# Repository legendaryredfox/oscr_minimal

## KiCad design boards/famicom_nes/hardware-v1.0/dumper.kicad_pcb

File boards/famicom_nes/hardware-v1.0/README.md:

# famicom_nes v1.0

Versão **v1.0** da placa [`famicom_nes`](../README.md): shield 100% THT para Arduino Mega 2560 R3, só USB. Versão anterior, mantida ao lado da mais nova.

| | |
|---|---|
| Slots | Famicom (60p) e NES (72p) em paralelo, 5 V; **um cartucho por vez, em um slot só** |
| Circuitos | Si5351, sem PIC. |
| Tamanho | 117,1 × 89,1 mm |
| Projeto KiCad | [`hardware-v1.0/`](.) (`dumper.kicad_pro`, `.kicad_sch`, `.kicad_pcb`) |
| Fábrica (JLCPCB) | `../fab/gerbers-v1.0/`, `../fab/dumper-v1.0-jlcpcb.zip` |
| Renders | `render-cima.png`, `render-baixo.png` |
| Estado | Nada montado nem testado com cartucho; revisar o layout no KiCad antes de encomendar |

## Troca de cartucho

O 5V dos slots vai direto do Mega e **não é cortado por software** (o desligamento por software foi retirado, D139). Para trocar o cartucho, **desligue a placa tirando o cabo USB** do Mega; nunca com a USB ligada.

## Proteção de corrente e tensão (D138)

**F1: fusível de vidro 5×20 mm de 500 mA (ação rápida) em suporte de clipes, opcional.** O suporte é de furo passante (Littelfuse série 100 ou equivalente) e o fusível queimado se troca **sem solda**; fica em série com o 5 V que a placa recebe do Mega Um curto no cartucho queima o fusível e protege a placa, o Mega e a porta USB. A queda é de 0,1 a 0,2 V a 200 mA (o SA-1 do SNES continua abaixo de ~5,2 V). **Sem o fusível no suporte a placa fica sem 5 V** (um fio no lugar dele também serve). Ele limita corrente e não protege contra tensão errada.

## Lista de peças

| Referências | Valor | Footprint | Qtd |
|---|---|---|---|
| A1 | Mega2560_R3_Shield | `dumper:Mega2560_R3_Shield` | 1 |
| C1 | 470u/16V | `Capacitor_THT:CP_Radial_D8.0mm_P3.50mm` | 1 |
| C2,C3 | 100n | `Capacitor_THT:C_Disc_D5.0mm_W2.5mm_P5.00mm` | 2 |
| D1 | LED 3mm | `LED_THT:LED_D3.0mm` | 1 |
| F1 | Fusivel 5x20 500mA | `Fuse:Fuseholder_Littelfuse_100_series_5x20mm` | 1 |
| FC1 | FC_Slot | `dumper:FC_Slot` | 1 |
| FLG1,FLG2 | PWR_FLAG | `` | 2 |
| NES1 | NES_Slot | `dumper:NES_Slot` | 1 |
| R1 | 220R | `Resistor_THT:R_Axial_DIN0207_L6.3mm_D2.5mm_P10.16mm_Horizontal` | 1 |
| U1 | Si5351_Module | `Connector_PinSocket_2.54mm:PinSocket_1x07_P2.54mm_Vertical` | 1 |

Gerada do esquemático desta versão (`kicad-cli sch export bom`). Peças marcadas DNP ou opcionais: `docs/bom.md` da placa.

## Verificação e fábrica (da raiz do repositório)

```
python3 tools/check_netlist.py --board famicom_nes boards/famicom_nes/hardware-v1.0/dumper.kicad_sch
kicad-cli sch erc boards/famicom_nes/hardware-v1.0/dumper.kicad_sch
kicad-cli pcb drc boards/famicom_nes/hardware-v1.0/dumper.kicad_pcb
tools/export_fab.sh famicom_nes v1.0
tools/render_board.sh famicom_nes v1.0 v1.1
```

Mais: [README da placa](../README.md), [`docs/`](../docs/).

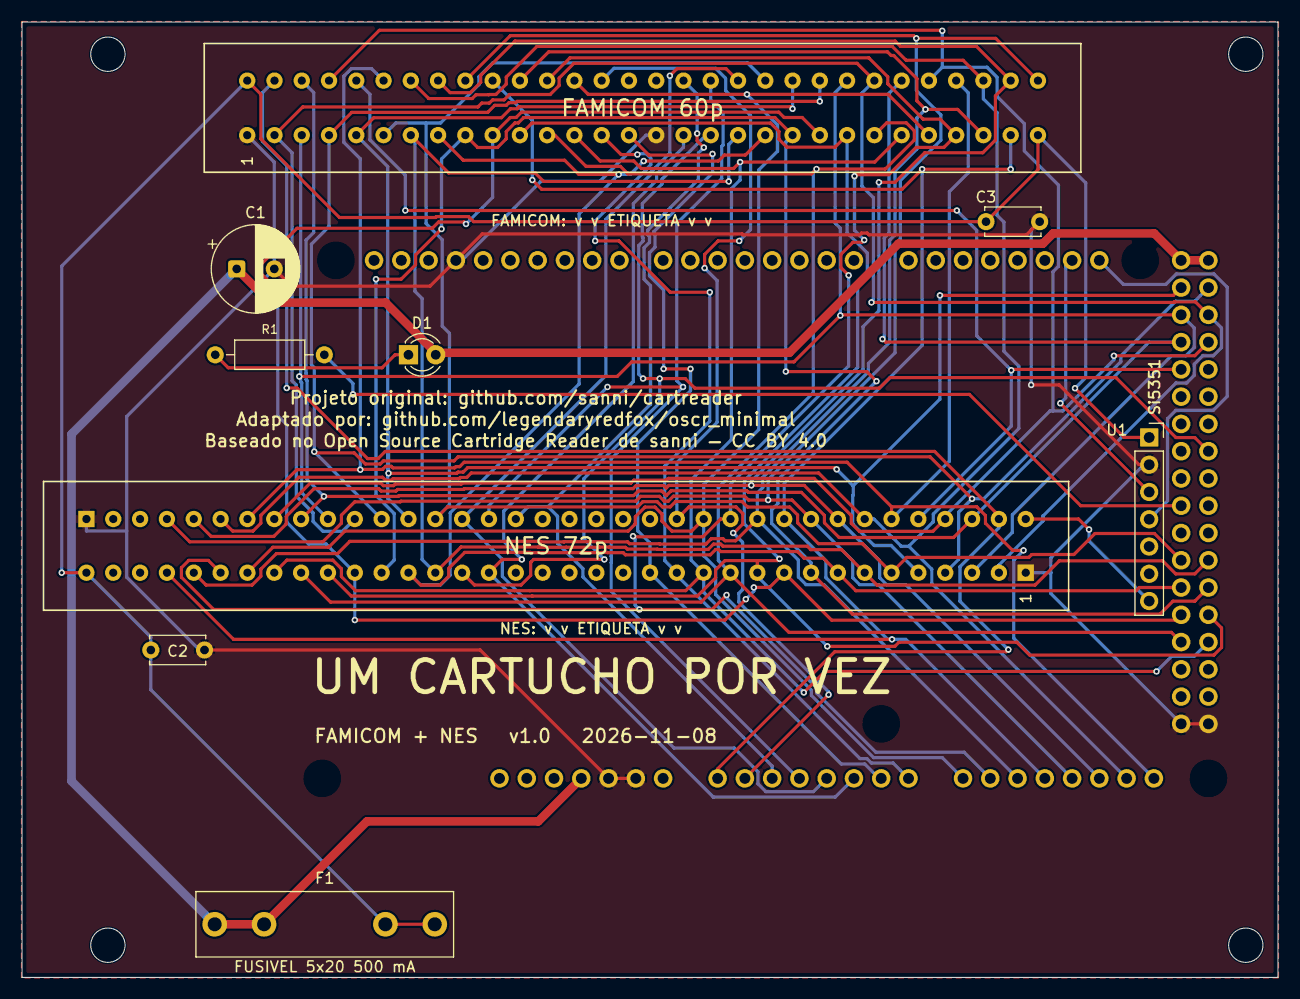
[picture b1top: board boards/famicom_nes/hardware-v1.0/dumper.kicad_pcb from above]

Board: 2 copper layers, 117.0 x 89.0 mm, 14 parts (0 on the bottom side), 40 nets.

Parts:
A1: Mega2560_R3_Shield
C1: 470u/16V; CP_Radial_D8.0mm_P3.50mm
C2, C3: 100n; C_Disc_D5.0mm_W2.5mm_P5.00mm
D1: LED 3mm; LED_D3.0mm
F1: Fusivel 5x20 500mA; Fuseholder_Littelfuse_100_series_5x20mm
FC1: FC_Slot
MH1, MH2, MH3, MH4: MountingHole_3.2mm; MountingHole_3.2mm_M3
NES1: NES_Slot
R1: 220R; R_Axial_DIN0207_L6.3mm_D2.5mm_P10.16mm_Horizontal
U1: Si5351_Module; PinSocket_1x07_P2.54mm_Vertical

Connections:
+5V: A1.5V1, A1.5V3, A1.5V4, C1.1, D1.2, F1.1
+5V_CART: C2.1, C3.1, F1.2, FC1.30, FC1.31, NES1.36, U1.1
/A0: A1.A0, FC1.32, NES1.38
/A1: A1.A1, FC1.44, NES1.50
/A2: A1.A2, FC1.47, NES1.56
/A3: A1.A3, FC1.48, NES1.57
/A4: A1.A4, FC1.49, NES1.58
/A5: A1.A5, FC1.17, NES1.21
/A6: A1.A6, FC1.15, NES1.15
/A7: A1.A7, FC1.14, NES1.14
/A8: A1.A8, FC1.26, FC1.43, NES1.30, NES1.49
/A9: A1.A9, FC1.27, FC1.42, NES1.31, NES1.48
/A10: A1.A10, FC1.28, FC1.41, NES1.32, NES1.47
/A11: A1.A11, FC1.29, FC1.40, NES1.33, NES1.46
/A12: A1.A12, FC1.39, FC1.60, NES1.45, NES1.69
/A13: A1.A13, FC1.38, FC1.59, NES1.44, NES1.68
/A14: A1.A14, FC1.37, FC1.58, NES1.43, NES1.67
/A15: A1.A15, FC1.36, FC1.57, NES1.42, NES1.66
/CLK0: NES1.37, U1.7
/D22: A1.D22, FC1.5, FC1.51, NES1.5, NES1.60
/D23: A1.D23, FC1.4, FC1.52, NES1.4, NES1.61
/D24: A1.D24, FC1.3, FC1.53, NES1.3, NES1.63
/D25: A1.D25, FC1.2, FC1.54, NES1.2, NES1.62
/D26: A1.D26, FC1.33, FC1.55, NES1.39, NES1.64
/D27: A1.D27, FC1.34, FC1.56, NES1.40, NES1.65
/D28: A1.D28, FC1.35, NES1.41
/D35: A1.D35, FC1.18, NES1.22
/D42: A1.D42, FC1.6, FC1.50, NES1.6, NES1.59
/D43: A1.D43, FC1.7, FC1.19, NES1.7, NES1.23
/D44: A1.D44, FC1.8, FC1.20, NES1.8, NES1.24
/D45: A1.D45, FC1.9, FC1.21, NES1.9, NES1.25
/D46: A1.D46, FC1.10, FC1.22, NES1.10, NES1.26
/D47: A1.D47, FC1.11, FC1.23, NES1.11, NES1.27
/D48: A1.D48, FC1.12, FC1.24, NES1.12, NES1.28
/D49: A1.D49, FC1.13, FC1.25, NES1.13, NES1.29
GND: A1.GND1, A1.GND2, A1.GND3, A1.GND5, A1.GND6, C1.2, C2.2, C3.2, FC1.1, FC1.16, NES1.1, NES1.72, U1.2
unnamed: A1.D38, R1.2
unnamed: D1.1, R1.1
unnamed: A1.D21, U1.4
unnamed: A1.D20, U1.3

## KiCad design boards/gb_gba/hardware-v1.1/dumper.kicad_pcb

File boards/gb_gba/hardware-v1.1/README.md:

# gb_gba v1.1

Versão **v1.1** da placa [`gb_gba`](../README.md): shield 100% THT para Arduino Mega 2560 R3, só USB. Esta é a versão mais nova.

| | |
|---|---|
| Slots | GBA (32 pads SMD, 1,5 mm), 3,3 V; GB e GBC só com adaptador |
| Circuitos | Sem Si5351 e sem PIC. |
| Tamanho | 138,1 × 77,1 mm |
| Desligar o 5V por software | **sim** |
| Projeto KiCad | [`hardware-v1.1/`](.) (`dumper.kicad_pro`, `.kicad_sch`, `.kicad_pcb`) |
| Fábrica (JLCPCB) | `../fab/gerbers-v1.1/`, `../fab/dumper-v1.1-jlcpcb.zip` |
| Renders | `render-cima.png`, `render-baixo.png` |
| Estado | Nada montado nem testado com cartucho; revisar o layout no KiCad antes de encomendar |

## Troca de cartucho

**Com desligamento por software** (bloco de troca de cartucho, D126): o comando `POWER` liga e desliga o 5V dos slots, o rail é descarregado e o LED amarelo "SEGURO TROCAR" acende quando dá para tirar o cartucho. Circuito, peças e testes: [`docs/referencia/bloco-troca.md`](../../../docs/referencia/bloco-troca.md).

## Proteção de corrente e tensão (D138)

**F1: fusível de vidro 5×20 mm de 500 mA (ação rápida) em suporte de clipes, opcional.** O suporte é de furo passante (Littelfuse série 100 ou equivalente) e o fusível queimado se troca **sem solda**; fica em série com o 5 V que a placa recebe do Mega (nas versões com bloco de troca, antes do Q1). Um curto no cartucho queima o fusível e protege a placa, o Mega e a porta USB. A queda é de 0,1 a 0,2 V a 200 mA (o SA-1 do SNES continua abaixo de ~5,2 V). **Sem o fusível no suporte a placa fica sem 5 V** (um fio no lugar dele também serve). Ele limita corrente e não protege contra tensão errada.

## O que muda em relação à v1.0

| Peça | Referências | Antes | Agora |
|---|---|---|---|
| LED verde 3mm | D2 | 0 | 1 |
| LED amarelo 3mm | D3 | 0 | 1 |
| IRF9540N | Q1 | 0 | 1 |
| 2N7000 | Q2,Q3 | 0 | 2 |
| 100k | R2,R7 | 0 | 2 |
| 100R | R3 | 0 | 1 |
| 1k | R4,R8,R9 | 0 | 3 |
| 330R | R5,R6 | 0 | 2 |

## Lista de peças

| Referências | Valor | Footprint | Qtd |
|---|---|---|---|
| A1 | Mega2560_R3_Shield | `dumper:Mega2560_R3_Shield` | 1 |
| C1 | 470u/16V | `Capacitor_THT:CP_Radial_D8.0mm_P3.50mm` | 1 |
| C2,C3 | 1u | `Capacitor_THT:C_Disc_D5.0mm_W2.5mm_P5.00mm` | 2 |
| C4 | 100n | `Capacitor_THT:C_Disc_D5.0mm_W2.5mm_P5.00mm` | 1 |
| D1 | LED 3mm | `LED_THT:LED_D3.0mm` | 1 |
| D2 | LED verde 3mm | `LED_THT:LED_D3.0mm` | 1 |
| D3 | LED amarelo 3mm | `LED_THT:LED_D3.0mm` | 1 |
| F1 | Fusivel 5x20 500mA | `Fuse:Fuseholder_Littelfuse_100_series_5x20mm` | 1 |
| FLG1,FLG2 | PWR_FLAG | `` | 2 |
| GBA1 | GBA_Slot | `dumper:GBA_Slot` | 1 |
| Q1 | IRF9540N | `Package_TO_SOT_THT:TO-220-3_Vertical` | 1 |
| Q2,Q3 | 2N7000 | `Package_TO_SOT_THT:TO-92_Inline` | 2 |
| R1 | 220R | `Resistor_THT:R_Axial_DIN0207_L6.3mm_D2.5mm_P10.16mm_Horizontal` | 1 |
| R2,R7 | 100k | `Resistor_THT:R_Axial_DIN0204_L3.6mm_D1.6mm_P2.54mm_Vertical` | 2 |
| R3 | 100R | `Resistor_THT:R_Axial_DIN0204_L3.6mm_D1.6mm_P2.54mm_Vertical` | 1 |
| R4,R8,R9 | 1k | `Resistor_THT:R_Axial_DIN0204_L3.6mm_D1.6mm_P2.54mm_Vertical` | 3 |
| R5,R6 | 330R | `Resistor_THT:R_Axial_DIN0204_L3.6mm_D1.6mm_P2.54mm_Vertical` | 2 |
| U1 | MCP1700-3302E/TO (3,3 V) | `Package_TO_SOT_THT:TO-92` | 1 |

Gerada do esquemático desta versão (`kicad-cli sch export bom`). Peças marcadas DNP ou opcionais: `docs/componentes-opcionais.md` da placa.

## Verificação e fábrica (da raiz do repositório)

```
python3 tools/check_netlist.py --board gb_gba
kicad-cli sch erc boards/gb_gba/hardware-v1.1/dumper.kicad_sch
kicad-cli pcb drc boards/gb_gba/hardware-v1.1/dumper.kicad_pcb
tools/export_fab.sh gb_gba v1.1
tools/render_board.sh gb_gba v1.0 v1.1
```

Mais: [README da placa](../README.md), [`docs/`](../docs/).

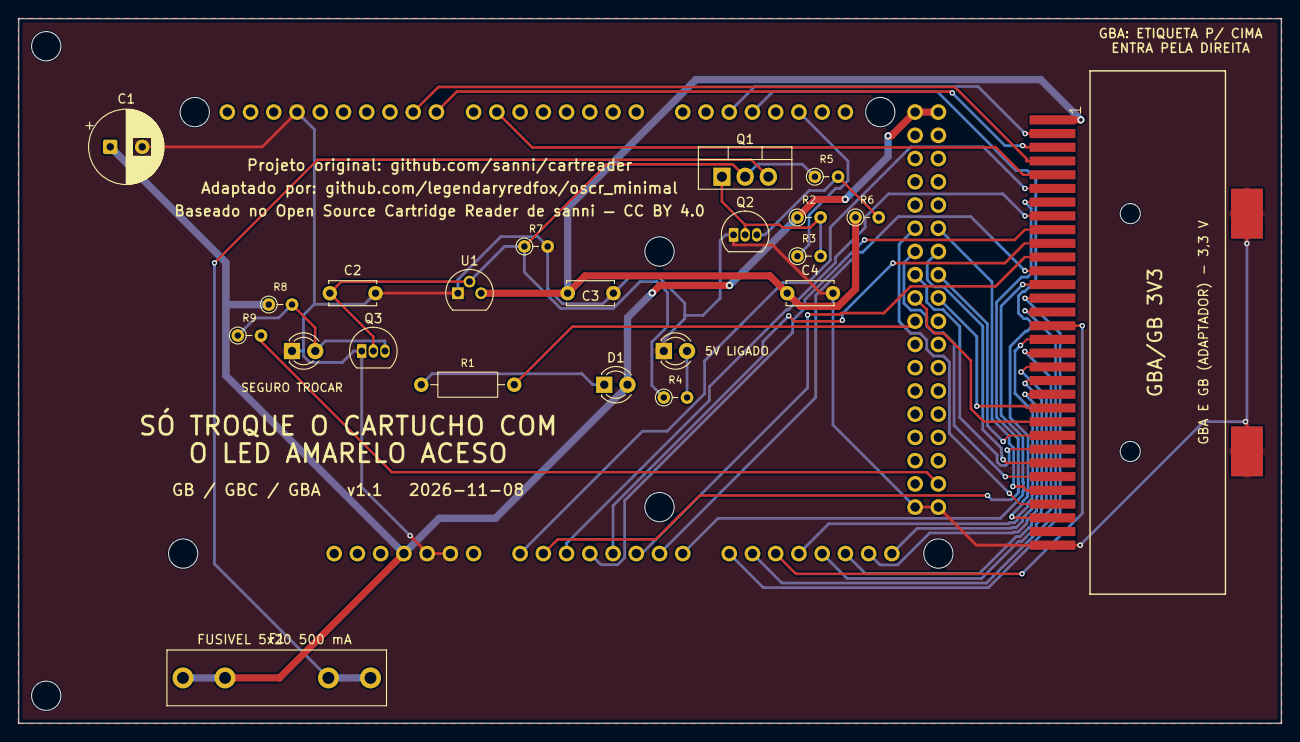
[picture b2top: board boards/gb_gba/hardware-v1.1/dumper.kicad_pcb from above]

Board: 2 copper layers, 138.0 x 77.0 mm, 25 parts (0 on the bottom side), 42 nets.

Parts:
A1: Mega2560_R3_Shield
C1: 470u/16V; CP_Radial_D8.0mm_P3.50mm
C2, C3: 1u; C_Disc_D5.0mm_W2.5mm_P5.00mm
C4: 100n; C_Disc_D5.0mm_W2.5mm_P5.00mm
D1: LED 3mm; LED_D3.0mm
D2: LED verde 3mm; LED_D3.0mm
D3: LED amarelo 3mm; LED_D3.0mm
F1: Fusivel 5x20 500mA; Fuseholder_Littelfuse_100_series_5x20mm
GBA1: GBA_Slot
MH1, MH3: MountingHole_3.2mm; MountingHole_3.2mm_M3
Q1: IRF9540N; TO-220-3_Vertical
Q2, Q3: 2N7000; TO-92_Inline
R1: 220R; R_Axial_DIN0207_L6.3mm_D2.5mm_P10.16mm_Horizontal
R2, R7: 100k; R_Axial_DIN0204_L3.6mm_D1.6mm_P2.54mm_Vertical
R3: 100R; R_Axial_DIN0204_L3.6mm_D1.6mm_P2.54mm_Vertical
R4, R8, R9: 1k; R_Axial_DIN0204_L3.6mm_D1.6mm_P2.54mm_Vertical
R5, R6: 330R; R_Axial_DIN0204_L3.6mm_D1.6mm_P2.54mm_Vertical
U1: MCP1700-3302E/TO (3,3 V); TO-92

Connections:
+3V3: C3.1, C4.1, GBA1.1, R6.1, U1.3
+5V: A1.5V1, A1.5V3, A1.5V4, C1.1, D1.2, F1.1, R2.1, R8.1
+5V_CART: C2.1, Q1.2, Q3.2, R4.1, R5.1, R7.1, U1.2
+5V_F: F1.2, Q1.3
/A0: A1.A0, GBA1.6
/A1: A1.A1, GBA1.7
/A2: A1.A2, GBA1.8
/A3: A1.A3, GBA1.9
/A4: A1.A4, GBA1.10
/A5: A1.A5, GBA1.11
/A6: A1.A6, GBA1.12
/A7: A1.A7, GBA1.13
/A8: A1.A8, GBA1.14
/A9: A1.A9, GBA1.15
/A10: A1.A10, GBA1.16
/A11: A1.A11, GBA1.17
/A12: A1.A12, GBA1.18
/A13: A1.A13, GBA1.19
/A14: A1.A14, GBA1.20
/A15: A1.A15, GBA1.21
/D6: A1.D6, GBA1.5
/D8: A1.D8, GBA1.3
/D9: A1.D9, GBA1.4
/D16: A1.D16, GBA1.2
/D17: A1.D17, GBA1.30
/D30: A1.D30, GBA1.29
/D31: A1.D31, GBA1.28
/D32: A1.D32, GBA1.27
/D33: A1.D33, GBA1.26
/D34: A1.D34, GBA1.25
/D35: A1.D35, GBA1.24
/D36: A1.D36, GBA1.23
/D37: A1.D37, GBA1.22
/PWR_EN: A1.D19, R3.1
/PWR_G: Q1.1, Q2.2, R2.2, R3.2
/SENSE: D3.2, Q3.3, R8.2, R9.1
/SENSE_MCU: A1.D53, R9.2
GND: A1.GND1, A1.GND2, A1.GND3, A1.GND5, A1.GND6, C1.2, C2.2, C3.2, C4.2, D2.1, D3.1, GBA1.32, GBA1.SHIELD_3, GBA1.SHIELD_4, Q2.1, Q3.1, R7.2, U1.1
unnamed: A1.D38, R1.2
unnamed: D1.1, R1.1
unnamed: D2.2, R4.2
unnamed: Q2.3, R5.2, R6.2

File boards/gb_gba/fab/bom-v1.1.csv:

"Ref","Valor","Footprint","Qtd"
"A1","Mega2560_R3_Shield","dumper:Mega2560_R3_Shield","1"
"C1","470u/16V","Capacitor_THT:CP_Radial_D8.0mm_P3.50mm","1"
"C2,C3","1u","Capacitor_THT:C_Disc_D5.0mm_W2.5mm_P5.00mm","2"
"C4","100n","Capacitor_THT:C_Disc_D5.0mm_W2.5mm_P5.00mm","1"
"D1","LED 3mm","LED_THT:LED_D3.0mm","1"
"D2","LED verde 3mm","LED_THT:LED_D3.0mm","1"
"D3","LED amarelo 3mm","LED_THT:LED_D3.0mm","1"
"F1","Fusivel 5x20 500mA","Fuse:Fuseholder_Littelfuse_100_series_5x20mm","1"
"FLG1,FLG2","PWR_FLAG","","2"
"GBA1","GBA_Slot","dumper:GBA_Slot","1"
"Q1","IRF9540N","Package_TO_SOT_THT:TO-220-3_Vertical","1"
"Q2,Q3","2N7000","Package_TO_SOT_THT:TO-92_Inline","2"
"R1","220R","Resistor_THT:R_Axial_DIN0207_L6.3mm_D2.5mm_P10.16mm_Horizontal","1"
"R2,R7","100k","Resistor_THT:R_Axial_DIN0204_L3.6mm_D1.6mm_P2.54mm_Vertical","2"
"R3","100R","Resistor_THT:R_Axial_DIN0204_L3.6mm_D1.6mm_P2.54mm_Vertical","1"
"R4,R8,R9","1k","Resistor_THT:R_Axial_DIN0204_L3.6mm_D1.6mm_P2.54mm_Vertical","3"
"R5,R6","330R","Resistor_THT:R_Axial_DIN0204_L3.6mm_D1.6mm_P2.54mm_Vertical","2"
"U1","MCP1700-3302E/TO (3,3 V)","Package_TO_SOT_THT:TO-92","1"

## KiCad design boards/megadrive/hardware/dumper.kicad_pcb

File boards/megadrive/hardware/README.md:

# megadrive v1.1

Versão **v1.1** da placa [`megadrive`](../README.md): shield 100% THT para Arduino Mega 2560 R3, só USB. Esta é a versão mais nova.

| | |
|---|---|
| Slots | Mega Drive (64p, 2,54 mm), 5 V |
| Circuitos | Si5351 e PIC12F629 (herdados da `16_bits`, ver `docs/componentes-opcionais.md`). |
| Tamanho | 107,1 × 65,1 mm |
| Desligar o 5V por software | **sim** |
| Projeto KiCad | [`hardware/`](.) (`dumper.kicad_pro`, `.kicad_sch`, `.kicad_pcb`) |
| Fábrica (JLCPCB) | `../fab/gerbers/`, `../fab/dumper-v1.1-jlcpcb.zip` |
| Renders | `../renders/megadrive-v1.1-cima.png`, `../renders/megadrive-v1.1-baixo.png` |
| Estado | Nada montado nem testado com cartucho; revisar o layout no KiCad antes de encomendar |

## Troca de cartucho

**Com desligamento por software** (bloco de troca de cartucho, D126): o comando `POWER` liga e desliga o 5V dos slots, o rail é descarregado e o LED amarelo "SEGURO TROCAR" acende quando dá para tirar o cartucho. Circuito, peças e testes: [`docs/referencia/bloco-troca.md`](../../../docs/referencia/bloco-troca.md).

## O que muda em relação à v1.0

| Peça | Referências | Antes | Agora |
|---|---|---|---|
| LED verde 3mm | D2 | 0 | 1 |
| LED amarelo 3mm | D3 | 0 | 1 |
| IRF9540N | Q1 | 0 | 1 |
| 2N7000 | Q2,Q3 | 0 | 2 |
| 100k | R2,R6 | 0 | 2 |
| 100R | R3 | 0 | 1 |
| 1k | R4,R7,R8 | 0 | 3 |
| 330R | R5 | 0 | 1 |

## Lista de peças

| Referências | Valor | Footprint | Qtd |
|---|---|---|---|
| A1 | Mega2560_R3_Shield | `dumper:Mega2560_R3_Shield` | 1 |
| C1 | 470u/16V | `Capacitor_THT:CP_Radial_D8.0mm_P3.50mm` | 1 |
| C2,C3,C4 | 100n | `Capacitor_THT:C_Disc_D5.0mm_W2.5mm_P5.00mm` | 3 |
| D1 | LED 3mm | `LED_THT:LED_D3.0mm` | 1 |
| D2 | LED verde 3mm | `LED_THT:LED_D3.0mm` | 1 |
| D3 | LED amarelo 3mm | `LED_THT:LED_D3.0mm` | 1 |
| FLG1,FLG2 | PWR_FLAG | `` | 2 |
| MD1 | MD_Slot | `dumper:MD_Slot` | 1 |
| Q1 | IRF9540N | `Package_TO_SOT_THT:TO-220-3_Vertical` | 1 |
| Q2,Q3 | 2N7000 | `Package_TO_SOT_THT:TO-92_Inline` | 2 |
| R1 | 220R | `Resistor_THT:R_Axial_DIN0207_L6.3mm_D2.5mm_P10.16mm_Horizontal` | 1 |
| R2,R6 | 100k | `Resistor_THT:R_Axial_DIN0204_L3.6mm_D1.6mm_P2.54mm_Vertical` | 2 |
| R3 | 100R | `Resistor_THT:R_Axial_DIN0204_L3.6mm_D1.6mm_P2.54mm_Vertical` | 1 |
| R4,R7,R8 | 1k | `Resistor_THT:R_Axial_DIN0204_L3.6mm_D1.6mm_P2.54mm_Vertical` | 3 |
| R5 | 330R | `Resistor_THT:R_Axial_DIN0204_L3.6mm_D1.6mm_P2.54mm_Vertical` | 1 |

Gerada do esquemático desta versão (`kicad-cli sch export bom`). Peças marcadas DNP ou opcionais: `docs/componentes-opcionais.md` da placa.

## Verificação e fábrica (da raiz do repositório)

```
python3 tools/check_netlist.py --board megadrive
kicad-cli sch erc boards/megadrive/hardware/dumper.kicad_sch
kicad-cli pcb drc boards/megadrive/hardware/dumper.kicad_pcb
tools/export_fab.sh megadrive v1.1
tools/render_board.sh megadrive v1.0 v1.1
```

Mais: [README da placa](../README.md), [`docs/`](../docs/).

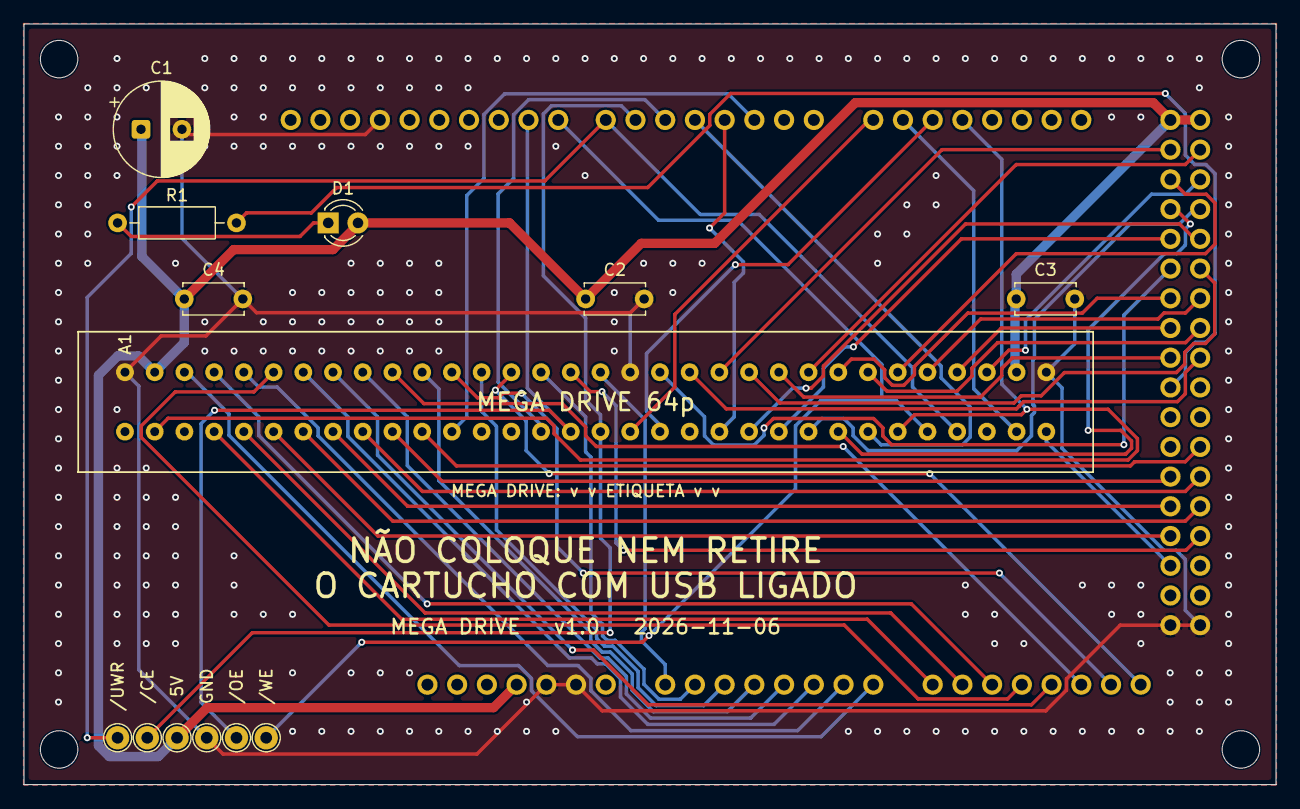
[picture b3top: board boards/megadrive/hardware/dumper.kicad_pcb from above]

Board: 2 copper layers, 107.0 x 65.0 mm, 18 parts (0 on the bottom side), 56 nets.

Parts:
A1: Mega2560_R3_Shield
C1: 470u/16V; CP_Radial_D8.0mm_P3.50mm
C2, C3, C4: 100n; C_Disc_D5.0mm_W2.5mm_P5.00mm
D1: LED 3mm; LED_D3.0mm
MD1: MD_Slot
MH1, MH2, MH3, MH4: MountingHole_3.2mm; MountingHole_3.2mm_M3
R1: 220R; R_Axial_DIN0207_L6.3mm_D2.5mm_P10.16mm_Horizontal
TP1: 5V; TestPoint_THTPad_D2.0mm_Drill1.0mm
TP2: GND; TestPoint_THTPad_D2.0mm_Drill1.0mm
TP3: /CE; TestPoint_THTPad_D2.0mm_Drill1.0mm
TP4: /OE; TestPoint_THTPad_D2.0mm_Drill1.0mm
TP5: /WE; TestPoint_THTPad_D2.0mm_Drill1.0mm
TP6: /UWR; TestPoint_THTPad_D2.0mm_Drill1.0mm

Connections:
/+5V: A1.5V1, A1.5V3, A1.5V4, C1.1, C2.1, C3.1, C4.1, D1.2, MD1.A2, MD1.A31, TP1.1
/A0: A1.A0, MD1.A17
/A1: A1.A1, MD1.A15
/A2: A1.A2, MD1.A13
/A3: A1.A3, MD1.A11
/A4: A1.A4, MD1.A9
/A5: A1.A5, MD1.A7
/A6: A1.A6, MD1.A5
/A7: A1.A7, MD1.A3
/A8: A1.A8, MD1.B4
/A9: A1.A9, MD1.B5
/A10: A1.A10, MD1.A4
/A11: A1.A11, MD1.A6
/A12: A1.A12, MD1.A8
/A13: A1.A13, MD1.A10
/A14: A1.A14, MD1.A12
/A15: A1.A15, MD1.A14
/CART: A1.D50, MD1.B32
/D2: A1.D2, MD1.B12
/D3: A1.D3, MD1.B21
/D4: A1.D4, MD1.B26
/D5: A1.D5, MD1.B15
/D6: A1.D6, MD1.B17, TP3.1
/D7: A1.D7, MD1.B29, TP6.1
/D8: A1.D8, MD1.B28, TP5.1
/D9: A1.D9, MD1.B16, TP4.1
/D14: A1.D14, MD1.B18
/D15: A1.D15, MD1.B31
/D16: A1.D16, MD1.B19
/D17: A1.D17, MD1.B2, MD1.B27
/D22: A1.D22, MD1.A21
/D23: A1.D23, MD1.A24
/D24: A1.D24, MD1.A27
/D25: A1.D25, MD1.A30
/D26: A1.D26, MD1.B25
/D27: A1.D27, MD1.B24
/D28: A1.D28, MD1.B23
/D29: A1.D29, MD1.B22
/D30: A1.D30, MD1.A19
/D31: A1.D31, MD1.A22
/D32: A1.D32, MD1.A25
/D33: A1.D33, MD1.A28
/D34: A1.D34, MD1.A29
/D35: A1.D35, MD1.A26
/D36: A1.D36, MD1.A23
/D37: A1.D37, MD1.A20
/D38: A1.D38, R1.2
/D43: A1.D43, MD1.B11
/D44: A1.D44, MD1.B10
/D45: A1.D45, MD1.B9
/D46: A1.D46, MD1.B8
/D47: A1.D47, MD1.B7
/D48: A1.D48, MD1.B6
/D49: A1.D49, MD1.A16
/GND: A1.GND1, A1.GND2, A1.GND3, A1.GND5, A1.GND6, C1.2, C2.2, C3.2, C4.2, MD1.A1, MD1.A18, MD1.A32, TP2.1
/LED_K: D1.1, R1.1

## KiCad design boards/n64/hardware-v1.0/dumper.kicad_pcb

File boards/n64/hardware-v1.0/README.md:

# n64 v1.0

Versão **v1.0** da placa [`n64`](../README.md): shield 100% THT para Arduino Mega 2560 R3, só USB. Esta é a versão mais nova.

| | |
|---|---|
| Slots | N64 (50 pinos), 3,3 V |
| Circuitos | Si5351 só para a EEPROM. |
| Tamanho | 110,1 × 75,1 mm |
| Projeto KiCad | [`hardware-v1.0/`](.) (`dumper.kicad_pro`, `.kicad_sch`, `.kicad_pcb`) |
| Fábrica (JLCPCB) | `../fab/gerbers-v1.0/`, `../fab/dumper-v1.0-jlcpcb.zip` |
| Renders | `render-cima.png`, `render-baixo.png` |
| Estado | Nada montado nem testado com cartucho; revisar o layout no KiCad antes de encomendar |

## Troca de cartucho

O 5V dos slots vai direto do Mega e **não é cortado por software** (o desligamento por software foi retirado, D139). Para trocar o cartucho, **desligue a placa tirando o cabo USB** do Mega; nunca com a USB ligada.

## Proteção de corrente e tensão (D138)

**F1: fusível de vidro 5×20 mm de 500 mA (ação rápida) em suporte de clipes, opcional.** O suporte é de furo passante (Littelfuse série 100 ou equivalente) e o fusível queimado se troca **sem solda**; fica em série com o 5 V que a placa recebe do Mega Um curto no cartucho queima o fusível e protege a placa, o Mega e a porta USB. A queda é de 0,1 a 0,2 V a 200 mA (o SA-1 do SNES continua abaixo de ~5,2 V). **Sem o fusível no suporte a placa fica sem 5 V** (um fio no lugar dele também serve). Ele limita corrente e não protege contra tensão errada.

## Lista de peças

| Referências | Valor | Footprint | Qtd |
|---|---|---|---|
| A1 | Mega2560_R3_Shield | `dumper:Mega2560_R3_Shield` | 1 |
| C1 | 470u/16V | `Capacitor_THT:CP_Radial_D8.0mm_P3.50mm` | 1 |
| C2,C3 | 1u | `Capacitor_THT:C_Disc_D5.0mm_W2.5mm_P5.00mm` | 2 |
| C4 | 100n | `Capacitor_THT:C_Disc_D5.0mm_W2.5mm_P5.00mm` | 1 |
| D1 | LED 3mm | `LED_THT:LED_D3.0mm` | 1 |
| F1 | Fusivel 5x20 500mA | `Fuse:Fuseholder_Littelfuse_100_series_5x20mm` | 1 |
| FLG1,FLG2 | PWR_FLAG | `` | 2 |
| N64_1 | N64_Slot | `dumper:N64_Slot` | 1 |
| R1 | 220R | `Resistor_THT:R_Axial_DIN0207_L6.3mm_D2.5mm_P10.16mm_Horizontal` | 1 |
| R2 | 1k | `Resistor_THT:R_Axial_DIN0207_L6.3mm_D2.5mm_P10.16mm_Horizontal` | 1 |
| U1 | Si5351_Module | `Connector_PinSocket_2.54mm:PinSocket_1x07_P2.54mm_Vertical` | 1 |
| U2 | MCP1700-3302E/TO (3,3 V) | `Package_TO_SOT_THT:TO-92` | 1 |

Gerada do esquemático desta versão (`kicad-cli sch export bom`). Peças marcadas DNP ou opcionais: `docs/bom.md` da placa.

## Verificação e fábrica (da raiz do repositório)

```
python3 tools/check_netlist.py --board n64 boards/n64/hardware-v1.0/dumper.kicad_sch
kicad-cli sch erc boards/n64/hardware-v1.0/dumper.kicad_sch
kicad-cli pcb drc boards/n64/hardware-v1.0/dumper.kicad_pcb
tools/export_fab.sh n64 v1.0
tools/render_board.sh n64 v1.0
```

Mais: [README da placa](../README.md), [`docs/`](../docs/).

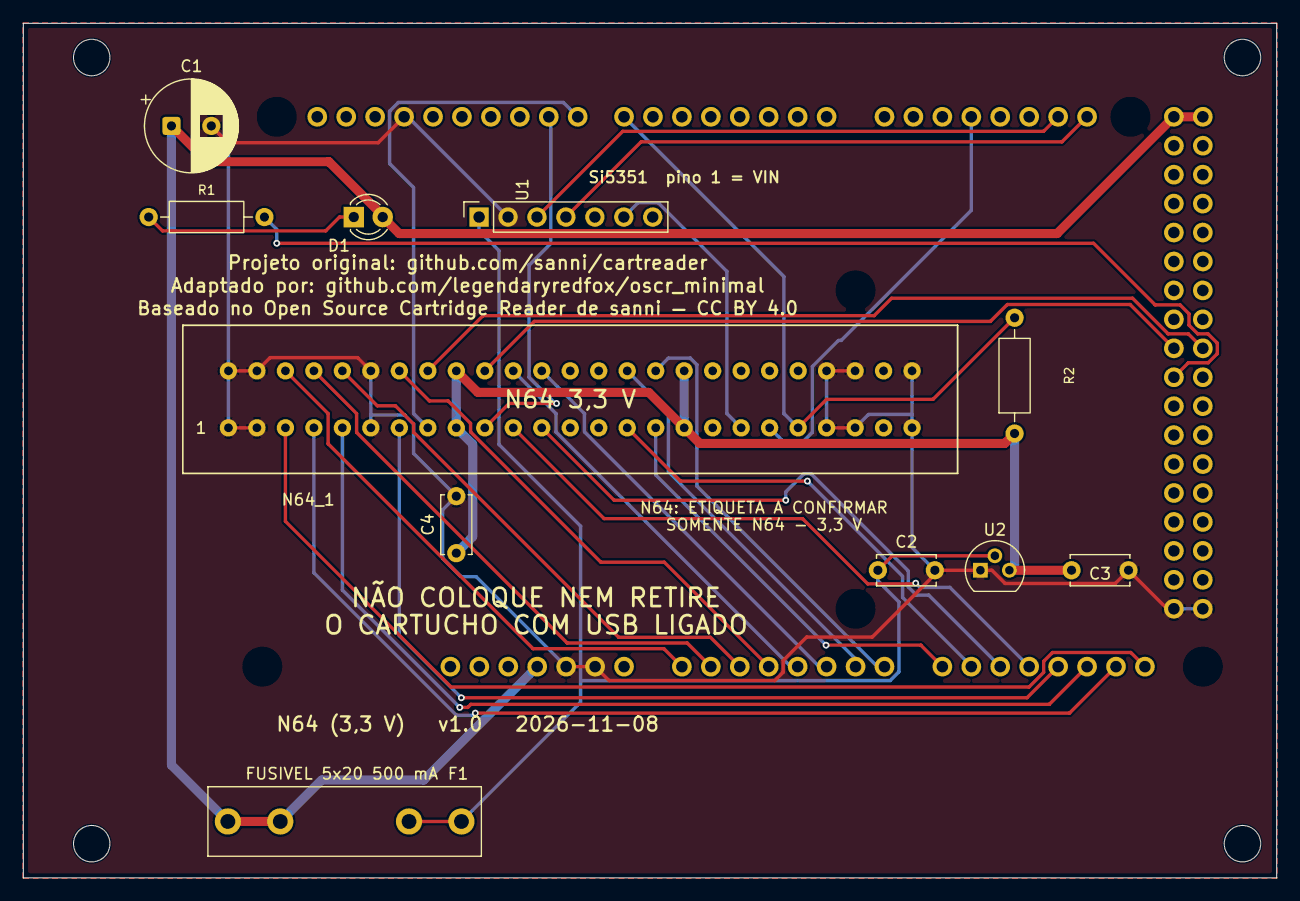
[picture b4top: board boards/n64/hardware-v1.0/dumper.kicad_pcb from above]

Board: 2 copper layers, 110.0 x 75.0 mm, 16 parts (0 on the bottom side), 31 nets.

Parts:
A1: Mega2560_R3_Shield
C1: 470u/16V; CP_Radial_D8.0mm_P3.50mm
C2, C3: 1u; C_Disc_D5.0mm_W2.5mm_P5.00mm
C4: 100n; C_Disc_D5.0mm_W2.5mm_P5.00mm
D1: LED 3mm; LED_D3.0mm
F1: Fusivel 5x20 500mA; Fuseholder_Littelfuse_100_series_5x20mm
MH1, MH2, MH3, MH4: MountingHole_3.2mm; MountingHole_3.2mm_M3
N64_1: N64_Slot
R1: 220R; R_Axial_DIN0207_L6.3mm_D2.5mm_P10.16mm_Horizontal
R2: 1k; R_Axial_DIN0207_L6.3mm_D2.5mm_P10.16mm_Horizontal
U1: Si5351_Module; PinSocket_1x07_P2.54mm_Vertical
U2: MCP1700-3302E/TO (3,3 V); TO-92

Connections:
+3V3: C3.1, C4.1, N64_1.9, N64_1.17, N64_1.34, N64_1.42, R2.1, U2.3
+5V: A1.5V1, A1.5V3, A1.5V4, C1.1, D1.2, F1.1
+5V_CART: C2.1, F1.2, U1.1, U2.2
/A0: A1.A0, N64_1.28
/A1: A1.A1, N64_1.29
/A2: A1.A2, N64_1.30
/A3: A1.A3, N64_1.32
/A4: A1.A4, N64_1.36
/A5: A1.A5, N64_1.37
/A6: A1.A6, N64_1.40
/A7: A1.A7, N64_1.41
/A8: A1.A8, N64_1.16
/A9: A1.A9, N64_1.15
/A10: A1.A10, N64_1.12
/A11: A1.A11, N64_1.11
/A12: A1.A12, N64_1.7
/A13: A1.A13, N64_1.5
/A14: A1.A14, N64_1.4
/A15: A1.A15, N64_1.3
/CLK1: N64_1.19, U1.6
/D7: A1.D7, N64_1.21, R2.2
/D8: A1.D8, N64_1.8
/D9: A1.D9, N64_1.10
/D17: A1.D17, N64_1.20
/D36: A1.D36, N64_1.35
/D37: A1.D37, N64_1.33
GND: A1.GND1, A1.GND2, A1.GND3, A1.GND5, A1.GND6, C1.2, C2.2, C3.2, C4.2, N64_1.1, N64_1.2, N64_1.6, N64_1.22, N64_1.23, N64_1.25, N64_1.26, N64_1.27, N64_1.31, N64_1.47, N64_1.48, N64_1.50, U1.2, U2.1
unnamed: A1.D38, R1.2
unnamed: D1.1, R1.1
unnamed: A1.D21, U1.4
unnamed: A1.D20, U1.3

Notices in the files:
boards/famicom_nes/hardware-v1.0/dumper.kicad_pcb:
Baseado no Open Source Cartridge Reader de sanni — CC BY 4.0
